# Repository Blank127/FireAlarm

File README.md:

# 🔥 Fire Alarm — Temperature Sensor Alarm System

> **CMPE2700 — PCB Design Project**
> STM32G0B1RETx · DS18B20 · DFRobot Gravity 7-Segment Displays · USB-C Powered

---

## Overview

A temperature monitoring and alarm system built on a custom PCB. The DS18B20 sensor continuously reads ambient temperature and displays it on a 4-digit 7-segment display. When the temperature exceeds a configurable threshold, an alarm LED activates. The alarm must be manually acknowledged by pressing the onboard button.

A second 7-segment display shows the current alarm threshold for reference at all times.

---

## Hardware

| Component | Description |
|---|---|
| **STM32G0B1RETx** | Main microcontroller |
| **DS18B20** | 1-Wire digital temperature sensor |
| **AMS1117-3.3** | LDO voltage regulator, steps down 5 V → 3.3 V |
| **DFRobot Gravity 4-Digit LED Display (×2)** | TM1650-based 7-segment displays over I2C |
| **USB-C Connector** | Board power input (5 V) |
| **SWD Header** | STM32 programming and debug interface |
| **Tactile Button** | Alarm acknowledge / reset |
| **External LED** | Alarm indicator |

---

## How It Works

1. The DS18B20 reads temperature every second over the 1-Wire bus
2. The current temperature is shown on **Display 1** (I2C1)
3. The alarm threshold is shown on **Display 2** (I2C2)
4. If the temperature exceeds the threshold, the **alarm LED turns on**
5. Press the **onboard button** to acknowledge and clear the alarm

---

## PCB

<!-- Replace the line below with your actual image once converted to PNG/JPG -->

> 📷 *PCB photo — upload a JPG/PNG version of the image to add it here*

### Known Hardware Issue — J1 / J2 Header Pin Swap

> ⚠️ **Workaround required — jumper wires needed**

The I2C headers J1 and J2 were routed with the following pinout:

```
PCB Header (J1/J2):   5V · GND · SDA · SCL
```

However, the mating female connectors on the DFRobot Gravity displays use:

```
Display Connector:    5V · GND · SCL · SDA
```

The **SDA and SCL lines are swapped** between the PCB header and the display connector. As a result, the displays cannot be plugged in directly — they will not communicate.

**Fix:** Use jumper wires to cross SDA and SCL between the header and the display connector before plugging in.

This will be corrected in the next PCB revision by swapping the SDA/SCL positions on J1 and J2 in the schematic.

---

## Firmware

The firmware is written in C using the STM32 HAL library and structured across three STM32CubeIDE projects:

| Project | Description |
|---|---|
| `Temperature sensor/` | DS18B20 driver development and test |
| `SevenSeg/` | TM1650 7-segment display driver development and test |
| `Temperature alert system/` | Final integrated alarm application |

### Firmware Repository Structure

```
Firmware/
├── Temperature sensor/         # DS18B20 test project
├── SevenSeg/                   # 7-segment display test project
└── Temperature alert system/   # Final alarm application
Hardware/
├── PCB_Final.kicad_pcb         # PCB layout
├── PCB_Final.kicad_sch         # Schematic
└── PCB_Final.kicad_pro         # KiCad project file
```

---

## Programming the STM32

1. Connect an ST-Link programmer to the **SWD header** on the PCB
2. Power the board via **USB-C**
3. Open the project in **STM32CubeIDE**
4. Build and flash using **Run → Debug** or **Run → Run**

---

## Pin Assignments

| Signal | STM32 Pin | Notes |
|---|---|---|
| 1-Wire Data | PA (one_wire_data) | DS18B20 with 4.7 kΩ pull-up |
| I2C1 SDA/SCL | I2C1 | Display 1 — current temperature |
| I2C2 SDA/SCL | I2C2 | Display 2 — alarm threshold |
| Alarm LED | PA (ext_led) | Active high |
| Button (B1) | PC13 | Active low, internal pull-up |
| Green LED | PA5 | Onboard status/heartbeat |
| USART2 TX/RX | PA2 / PA3 | Debug output at 115200 baud |

---

## Author

**Aldrich Dias** — CMPE2750, 2026

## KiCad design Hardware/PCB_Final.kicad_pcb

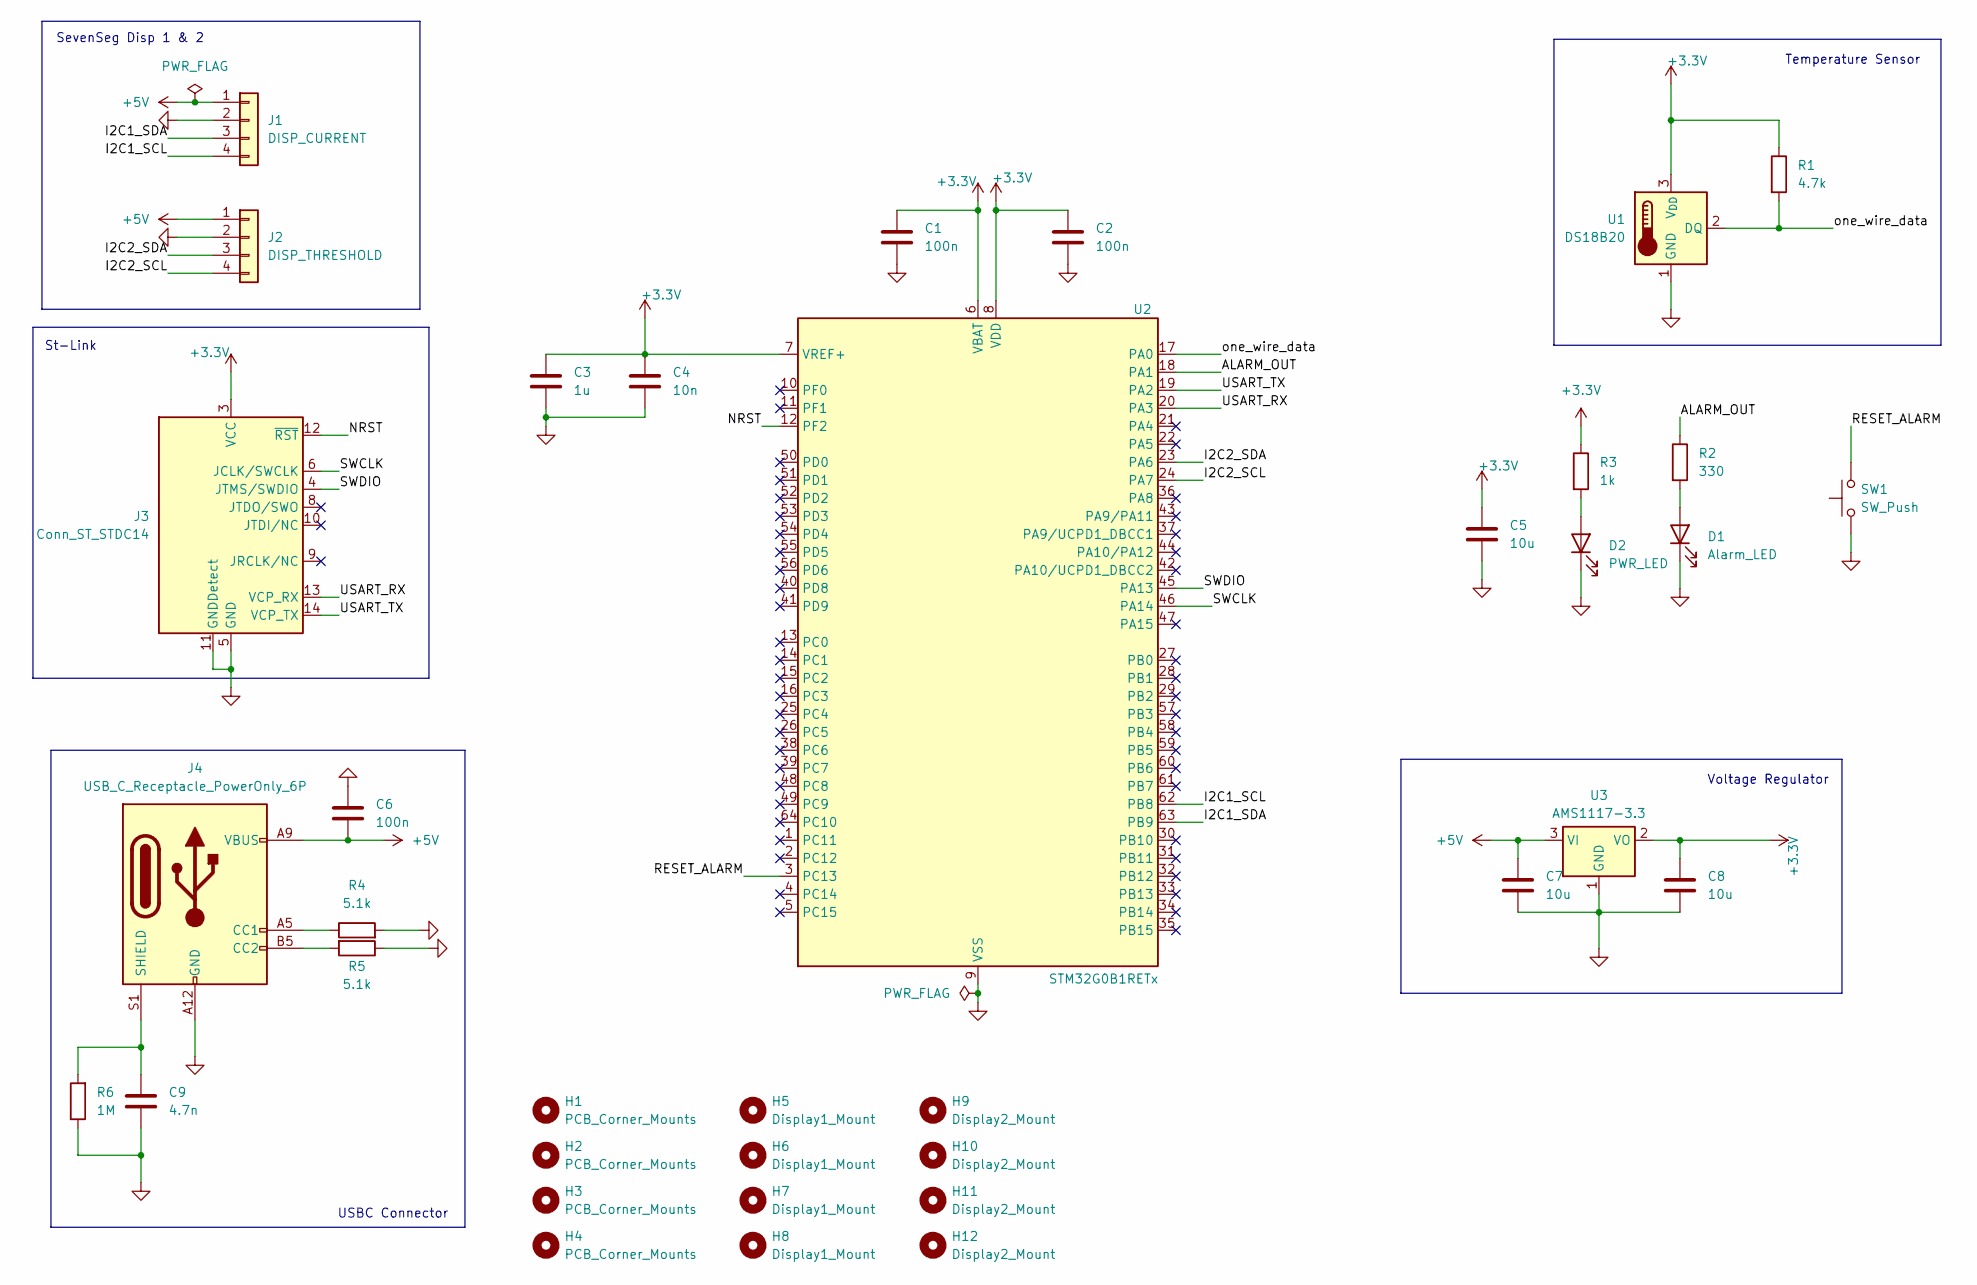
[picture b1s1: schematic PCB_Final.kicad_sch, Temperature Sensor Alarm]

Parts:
C1, C2, C6: 100n; C_0402_1005Metric
C3: 1u; C_0402_1005Metric
C4: 10n; C_0402_1005Metric
C5, C7, C8: 10u; C_0805_2012Metric
C9: 4.7n; C_0402_1005Metric
D1: Alarm_LED; LED_D3.0mm
D2: PWR_LED; LED_D3.0mm
H1, H2, H3, H4: PCB_Corner_Mounts; MountingHole_3.2mm_M3
H5, H6, H7, H8: Display1_Mount; MountingHole_3.2mm_M3
H9, H10, H11, H12: Display2_Mount; MountingHole_3.2mm_M3
J1: DISP_CURRENT; PinHeader_1x04_P2.54mm_Vertical
J2: DISP_THRESHOLD; PinHeader_1x04_P2.54mm_Vertical
J3: Conn_ST_STDC14; PinHeader_2x07_P1.27mm_Vertical
J4: USB_C_Receptacle_PowerOnly_6P; USB_C_Receptacle_GCT_USB4125-xx-x-0190_6P_TopMnt_Horizontal
R1: 4.7k; R_0402_1005Metric
R2: 330; R_0402_1005Metric
R3: 1k; R_0402_1005Metric
R4, R5: 5.1k; R_0402_1005Metric
R6: 1M; R_0402_1005Metric
SW1: SW_Push; SW_Tactile_SPST_Angled_PTS645Vx31-2LFS
U1: DS18B20; TO-92_Inline
U2: STM32G0B1RETx; LQFP-64_10x10mm_P0.5mm
U3: AMS1117-3.3; SOT-223-3_TabPin2

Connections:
+3.3V: C1.1, C2.1, C3.1, C4.1, C5.1, C8.1, J3.3 (VCC), R1.1, R3.1, U1.3 (V_{DD}), U2.6 (VBAT), U2.7 (VREF+), U2.8 (VDD), U3.2 (VO)
+5V: C6.2, C7.1, J1.1, J2.1, J4.A9 (VBUS), J4.B9 (VBUS), U3.3 (VI)
/ALARM_OUT: R2.1, U2.18 (PA1)
/I2C1_SCL: J1.4, U2.62 (PB8)
/I2C1_SDA: J1.3, U2.63 (PB9)
/I2C2_SCL: J2.4, U2.24 (PA7)
/I2C2_SDA: J2.3, U2.23 (PA6)
/NRST: J3.12 (~RST), U2.12 (PF2)
/RESET_ALARM: SW1.2, U2.3 (PC13)
/SWCLK: J3.6 (JCLK/SWCLK), U2.46 (PA14)
/SWDIO: J3.4 (JTMS/SWDIO), U2.45 (PA13)
/USART_RX: J3.13 (VCP_RX), U2.20 (PA3)
/USART_TX: J3.14 (VCP_TX), U2.19 (PA2)
/one_wire_data: R1.2, U1.2 (DQ), U2.17 (PA0)
GND: C1.2, C2.2, C3.2, C4.2, C5.2, C6.1, C7.2, C8.2, C9.2, D1.1 (K), D2.1 (K), J1.2, J2.2, J3.5 (GND), J3.7 (GND), J3.11 (GNDDetect), J4.A12 (GND), J4.B12 (GND), R4.2, R5.1, R6.1, SW1.1, U1.1 (GND), U2.9 (VSS), U3.1 (GND)
unnamed: D1.2 (A), R2.2
unnamed: D2.2 (A), R3.2
unnamed: J4.A5 (CC1), R4.1
unnamed: J4.B5 (CC2), R5.2
unnamed: C9.1, J4.S1 (SHIELD), R6.2

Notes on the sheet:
St-Link
USBC Connector
Temperature Sensor
Voltage Regulator
SevenSeg Disp 1 & 2

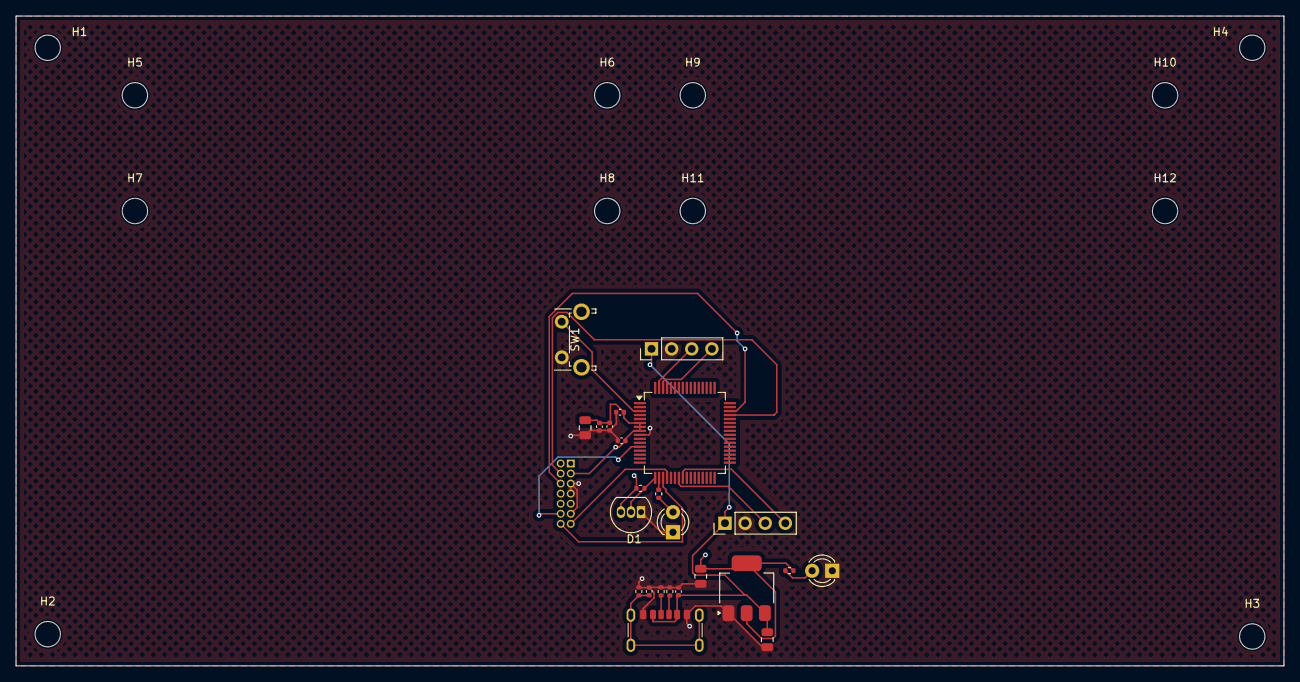
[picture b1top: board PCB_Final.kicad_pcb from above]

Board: 4 copper layers, 160.0 x 82.0 mm, 37 parts (1 on the bottom side), 20 nets.

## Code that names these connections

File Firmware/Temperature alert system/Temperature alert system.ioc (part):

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Mcu.Name=STM32G0B1R(B-C-E)Tx
Mcu.Package=LQFP64
Mcu.UserName=STM32G0B1RETx
PA0.GPIOParameters=GPIO_PuPd,GPIO_Label,GPIO_ModeDefaultOutputPP
PA0.GPIO_Label=one_wire_data
PA0.GPIO_ModeDefaultOutputPP=GPIO_MODE_OUTPUT_OD
PA0.GPIO_PuPd=GPIO_NOPULL
PA0.Signal=GPIO_Output
PA1.GPIOParameters=GPIO_PuPd,GPIO_Label
PA1.GPIO_Label=ext_led
PA1.GPIO_PuPd=GPIO_PULLUP
PA1.Signal=GPIO_Output
PA13.GPIOParameters=GPIO_Label
PA13.GPIO_Label=TMS
PA13.Mode=Serial_Wire
PA13.Signal=SYS_SWDIO
PA14-BOOT0.GPIOParameters=GPIO_Label
PA14-BOOT0.GPIO_Label=TCK
PA14-BOOT0.Mode=Serial_Wire
PA14-BOOT0.Signal=SYS_SWCLK
PA2.GPIOParameters=GPIO_Label
PA2.GPIO_Label=USART2_TX [STLK_TX]
PA2.Mode=Asynchronous
PA2.Signal=USART2_TX
PA3.GPIOParameters=GPIO_Label
PA3.GPIO_Label=USART2_RX [STLK_RX]
PA3.Mode=Asynchronous
PA3.Signal=USART2_RX
PA5.GPIOParameters=GPIO_Speed,GPIO_Label
PA5.GPIO_Label=LED_GREEN
PA5.GPIO_Speed=GPIO_SPEED_FREQ_HIGH
PA5.Signal=GPIO_Output
PA6.Mode=I2C
PA6.Signal=I2C2_SDA
PA7.Mode=I2C
PA7.Signal=I2C2_SCL
PB8.Mode=I2C
PB8.Signal=I2C1_SCL
PB9.Mode=I2C
PB9.Signal=I2C1_SDA
PC13.GPIOParameters=GPIO_PuPd,GPIO_Label,GPIO_ModeDefaultEXTI
PC13.GPIO_Label=B1 [blue push button]
PC13.GPIO_ModeDefaultEXTI=GPIO_MODE_IT_FALLING
PC13.GPIO_PuPd=GPIO_PULLUP
PC13.Signal=GPXTI13
PC14-OSC32_IN\ (PC14).Mode=LSE-External-Oscillator
PC14-OSC32_IN\ (PC14).Signal=RCC_OSC32_IN
PC15-OSC32_OUT\ (PC15).Mode=LSE-External-Oscillator
PC15-OSC32_OUT\ (PC15).Signal=RCC_OSC32_OUT
PF0-OSC_IN\ (PF0).GPIOParameters=GPIO_Label
PF0-OSC_IN\ (PF0).GPIO_Label=MCO
PF0-OSC_IN\ (PF0).Mode=HSE-External-Clock-Source
PF0-OSC_IN\ (PF0).Signal=RCC_OSC_IN
RCC.HSE_VALUE=8000000
RCC.SYSCLKFreq_VALUE=16000000
board=NUCLEO-G0B1RE
boardIOC=true

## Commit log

2026-05-11 Add initial README for FireAlarm project
2026-05-11 Create gitignore
2026-05-11 added firmware
2026-05-11 Deleted firmware
2026-05-11 fixed gitignore
2026-05-11 Add three STM32 firmware projects
    Import initial STM32CubeIDE firmware for three projects: SevenSeg, Temperature sensor, and Temperature alert system. Adds project metadata (.project, .cproject, .mxproject, .ioc) plus Core and Startu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
2026-05-11 Add KiCad final PCB, schematic and project
    Add complete KiCad project files for the final PCB: Hardware/PCB_Final.kicad_pcb, Hardware/PCB_Final.kicad_sch and Hardware/PCB_Final.kicad_pro. Includes KiCad 9 board file with layer stackup, nets (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
2026-05-12 Use Markdown image in README and update PCB photo
    Replace the HTML <img> tag in README.md with a Markdown image reference for the PCB photo and remove the inline rotate(180deg) style so the image displays normally. The binary images/pcb.jpg was also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
2026-05-13 Add MIT License to the project
2026-05-13 Update course code from CMPE2700 to CMPE2750
